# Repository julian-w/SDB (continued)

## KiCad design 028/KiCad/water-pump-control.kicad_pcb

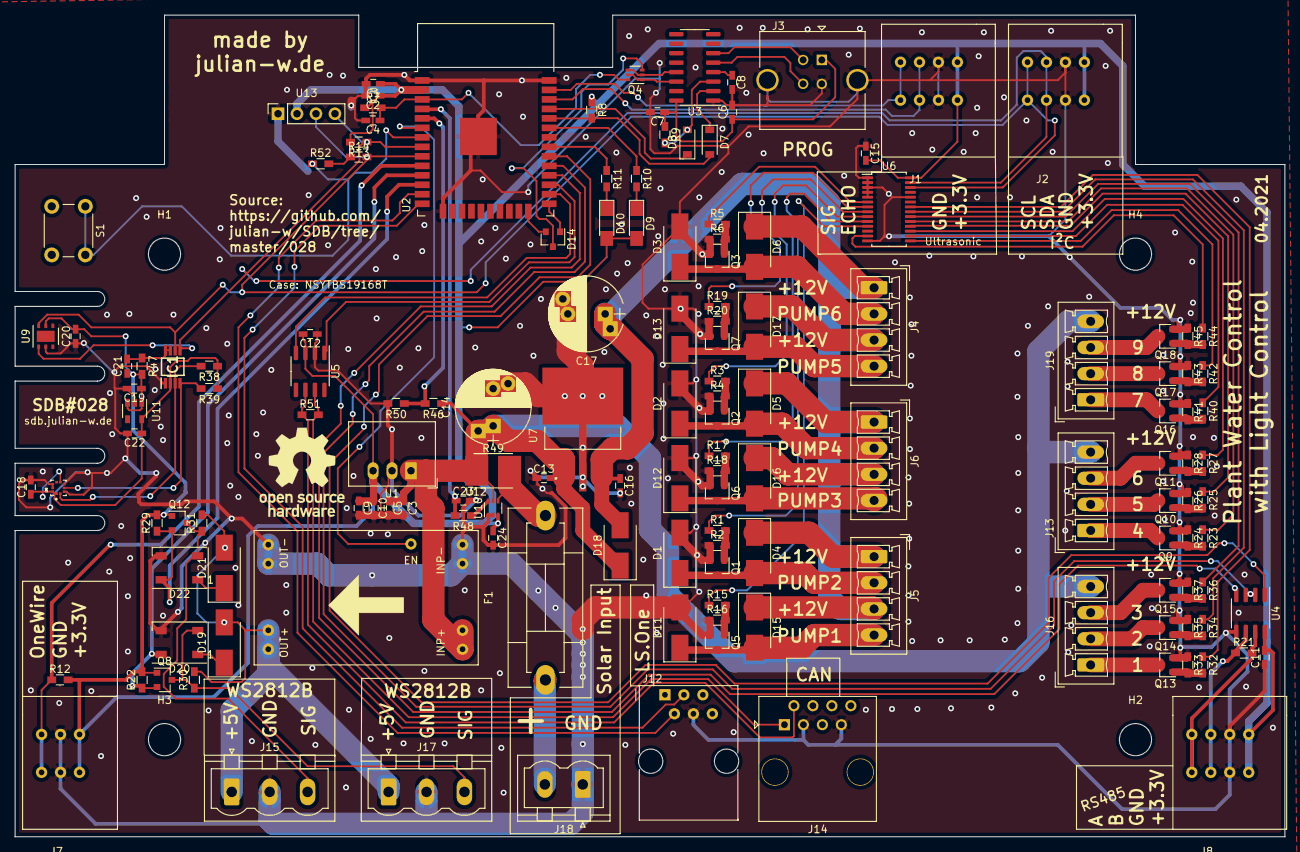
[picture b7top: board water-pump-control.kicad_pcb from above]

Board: 2 copper layers, 170.0 x 110.0 mm, 153 parts (0 on the bottom side), 101 nets.

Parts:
C1, C2, C5, C6, C7, C10, C11, C12, C13, C15, C16, C18, C20, C21: 100n; C_0603_HandSoldering
C3, C9: 10u; C_0603_HandSoldering
C4, C19, C22: 1u; C_0603_HandSoldering
C8: 10n; C_0603_HandSoldering
C14, C17: 100u; CP_Radial_D10.0mm_P5.00mm_P7.50mm
C23: 10nF; C_0603_HandSoldering
C24: 100nF; C_0603_HandSoldering
D1, D2, D3, D4, D5, D6, D11, D12, D13, D15, D16, D17, D18, D19, D21: 1N4004; D_SMB_Handsoldering
D7, D8: D; D_SOD-123
D9, D10: LED; LED_1206_HandSoldering
D14: BAT54C; SOT-23
D20, D22: WS2812B; LED_WS2812B_PLCC4_5.0x5.0mm_P3.2mm
F1: Fuse; Fuseholder5x20_horiz_SemiClosed_Casing10x25mm
H1, H2, H3, H4: MountingHole; MountingHole_4.3mm_M4
IC1: NVT2002DP,118; SOP65P490X110-8N
J1, J2, J8: Screw_Terminal_01x04; 4x2-2.54
J3: USB_B; USB_B_TE_5787834_Vertical
J4, J5, J6, J13, J16, J19: Screw_Terminal_01x04; PhoenixContact_MCV_1,5_4-G-3.5_1x04_P3.50mm_Vertical
J7: Screw_Terminal_01x03; 3x2-2.54
J12: 6P6C; RJ12_Amphenol_54601
J14: 8P8C; RJ45_OST_PJ012-8P8CX_Vertical
J15, J17: Screw_Terminal_01x03; PhoenixContact_MSTBVA_2,5_3-G-5,08_1x03_P5.08mm_Vertical
J18: BAT; PhoenixContact_MSTBVA_2,5_2-G-5,08_1x02_P5.08mm_Vertical
LOGO1: OSHW-LOGOL; OSHW-Logo_11.4x12mm_SilkScreen
Q1, Q2, Q3, Q5, Q6, Q7, Q9, Q10, Q11, Q13, Q14, Q15, Q16, Q17, Q18: IRLML6344; SOT-23
Q4: PUMX1; SOT-363_SC-70-6
Q8, Q12: BSS138; SOT-23
R1, R3, R5, R15, R17, R19, R23, R25, R27, R32, R34, R36, R40, R42, R44: 100; R_0603_HandSoldering
R2, R4, R6, R7, R8, R9, R16, R18, R20, R22, R24, R26, R28, R29, R30, R31, R33, R35, R37, R41, R43, R45, R52: 10k; R_0603_HandSoldering
R10, R11: 470; R_0603_HandSoldering
R12, R13, R14, R38, R39: 4.7k; R_0603_HandSoldering
R21, R51: 120; R_0603_HandSoldering
R46, R47: 200k; R_0603_HandSoldering
R48: 2.2k; R_0603_HandSoldering
R49: 2m; R_Bourns_CRE2512
R50: 20k; R_0603_HandSoldering
S1: SWITCH-MOMENTARY-2SMD; SW_PUSH_6mm_H13mm
U1: R-78HB3.3-0.5; Converter_DCDC_RECOM_R-78HB-0.5_THT
U2: ESP32-WROOM-32
U3: CH340C; SOIC-16_3.9x9.9mm_P1.27mm
U4: MAX14783ExS; SOIC-8_3.9x4.9mm_P1.27mm
U5: SN65HVD232; SOIC-8_3.9x4.9mm_P1.27mm
U6: PCA9685PW; TSSOP-28_4.4x9.7mm_P0.65mm
U7: LM2940S-12_NOPB; TO254P1524X483-4N
U8: BMP388; PQFN50P200X200X80-10N
U9: HDC1080; Texas_PWSON-N6
U10: INA186; SOT-363_SC-70-6
U11: MIC5504-1.8YM5; SOT-23-5
U12: 5V5A
U13: OLED_I2C; OLED_SSD1306_I2C_0.96

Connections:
5V_EN: U2.6, U12.5
+1V8: C18.1, C22.1, IC1.2, R38.1, R39.1, U8.1, U8.6, U8.10, U11.5
+3V3: C1.1, C2.1, C9.1, C10.1, C11.2, C12.2, C15.2, C19.1, C20.2, C21.1, C24.1, D9.2, D10.2, J1.4, J2.4, J7.3, J8.4, Q8.1, Q12.1, R7.1, R8.1, R12.2, R13.2, R14.1, R22.2, R29.2, R47.2, R52.2, U1.3, U2.2, U4.8, U5.3, U6.28, U9.5, U10.3, U11.1, U11.3, U13.2
+5V: D19.2, D21.2, J15.1, J17.1, R30.2, R31.2, U12.3
+5VP: C6.1, C7.1, J3.1, R9.1, U3.16
+12V: C16.1, C17.1, D4.1, D5.1, D6.1, D15.1, D16.1, D17.1, D18.2, J4.1, J4.3, J5.1, J5.3, J6.1, J6.3, U7.3
+15V: C3.1, C5.1, C13.2, C14.1, D18.1, J13.4, J16.4, J19.4, R46.1, R49.1, U1.1, U7.1, U10.5, U12.1
/SCL_1V8: IC1.3, R38.2, U8.2
/SDA_1V8: IC1.4, R39.2, U8.4
/SHUNT_LOAD_P: F1.2, R49.2, U10.4
CANH: J14.1, R51.2, U5.7
CANL: J14.2, R51.1, U5.6
CAN_D: U2.27, U5.1
CAN_R: U2.26, U5.4
GND: C1.2, C2.2, C3.2, C4.2, C5.2, C6.2, C7.2, C8.2, C9.2, C10.2, C11.1, C12.1, C13.1, C14.2, C15.1, C16.2, C17.2, C18.2, C19.2, C20.1, C22.2, C23.2, C24.2, D1.2, D2.2, D3.2, D11.2, D12.2, D13.2, D20.3, D22.3, IC1.1, J1.3, J2.3, J3.4, J3.5, J7.2, J8.3, J12.4, J14.3, J14.7, J15.2, J17.2, J18.1, Q1.2, Q2.2, Q3.2, Q5.2, Q6.2, Q7.2, Q9.2, Q10.2, Q11.2, Q13.2, Q14.2, Q15.2, Q16.2, Q17.2, Q18.2, R2.1, R4.1, R6.1, R16.1, R18.1, R20.1, R24.1, R26.1, R28.1, R33.1, R35.1, R37.1, R41.1, R43.1, R45.1, R50.2, U1.2, U2.1, U2.15, U2.38, U2.39, U3.1, U4.5, U5.2, U6.1, U6.2, U6.3, U6.4, U6.5, U6.14, U6.24, U7.2, U7.4, U8.3, U8.5, U8.8, U8.9, U9.2, U10.1, U10.2, U11.2, U12.2, U12.4, U13.1
IO0: D14.1, U2.25
IO2: D14.2, U2.24
I_LOAD: C23.1, R48.2, U2.4
LED1: R23.1, U6.19
LED2: R25.1, U6.18
LED3: R27.1, U6.17
LED4: R32.1, U6.22
LED5: R34.1, U6.21
LED6: R36.1, U6.20
LED7: R40.1, U6.16
LED8: R42.1, U6.15
LED9: R44.1, U6.13
LSONE_RX: J12.3, U2.14
LSONE_TX: J12.2, U2.13
unnamed: C8.1, U3.4
unnamed: C21.2, IC1.7, IC1.8, R47.1
unnamed: D1.1, D4.2, J5.2, Q1.3
unnamed: D2.1, D5.2, J6.2, Q2.3
unnamed: D3.1, D6.2, J4.2, Q3.3
unnamed: D7.1, U3.2
unnamed: D8.2, R9.2, U3.3
unnamed: D9.1, R10.2
unnamed: D10.1, R11.2
unnamed: D11.1, D15.2, J5.4, Q5.3
unnamed: D12.1, D16.2, J6.4, Q6.3
unnamed: D13.1, D17.2, J4.4, Q7.3
unnamed: D14.3, Q4.3
unnamed: D19.1, D20.1
unnamed: D21.1, D22.1
unnamed: F1.1, J18.2
unnamed: J3.2, U3.6
unnamed: J3.3, U3.5
unnamed: J13.1, Q9.3
unnamed: J13.2, Q10.3
unnamed: J13.3, Q11.3
unnamed: J16.1, Q13.3
unnamed: J16.2, Q14.3
unnamed: J16.3, Q15.3
unnamed: J19.1, Q16.3
unnamed: J19.2, Q17.3
unnamed: J19.3, Q18.3
unnamed: Q1.1, R1.2, R2.2
unnamed: Q2.1, R3.2, R4.2
unnamed: Q3.1, R5.2, R6.2
unnamed: Q4.1, Q4.5, U3.14
unnamed: Q4.2, Q4.4, U3.13
unnamed: Q5.1, R15.2, R16.2
unnamed: Q6.1, R17.2, R18.2
unnamed: Q7.1, R19.2, R20.2
unnamed: Q9.1, R23.2, R24.2
unnamed: Q10.1, R25.2, R26.2
unnamed: Q11.1, R27.2, R28.2
unnamed: Q13.1, R32.2, R33.2
unnamed: Q14.1, R34.2, R35.2
unnamed: Q15.1, R36.2, R37.2
unnamed: Q16.1, R40.2, R41.2
unnamed: Q17.1, R42.2, R43.2
unnamed: Q18.1, R44.2, R45.2
unnamed: R48.1, U10.6
unnamed: R52.1, S1.1, U2.7
ONEWIRE: J7.1, R12.1, U2.10
PUMP1: R1.1, U6.10
PUMP2: R3.1, U6.8
PUMP3: R5.1, U6.6
PUMP4: R15.1, U6.11
PUMP5: R17.1, U6.9
PUMP6: R19.1, U6.7
RESET: C4.1, Q4.6, R7.2, U2.3
RS485_A: J8.1, R21.2, U4.7
RS485_B: J8.2, R21.1, U4.6
RS485_DIR: U2.29, U4.2, U4.3
RS485_RX: U2.30, U4.1
RS485_TX: U2.28, U4.4
SCL: IC1.6, J2.1, R14.2, U2.9, U6.26, U9.6, U13.3
SDA: IC1.5, J2.2, R13.1, U2.8, U6.27, U9.1, U13.4
SONIC_ECHO: J1.2, U2.36
SONIC_TRIG: J1.1, U2.37
STAT1: R10.1, U2.33
STAT2: R11.1, U2.31
USB_RX: D8.1, U2.35
USB_TX: D7.2, R8.2, U2.34
V_LOAD: R46.2, R50.1, U2.5
WS2812_IN1: D22.4, Q12.2, R29.1, U2.12
WS2812_IN2: D20.4, Q8.2, R22.1, U2.11
WS2812_OUT1: D22.2, J15.3, Q12.3, R31.1
WS2812_OUT2: D20.2, J17.3, Q8.3, R30.1

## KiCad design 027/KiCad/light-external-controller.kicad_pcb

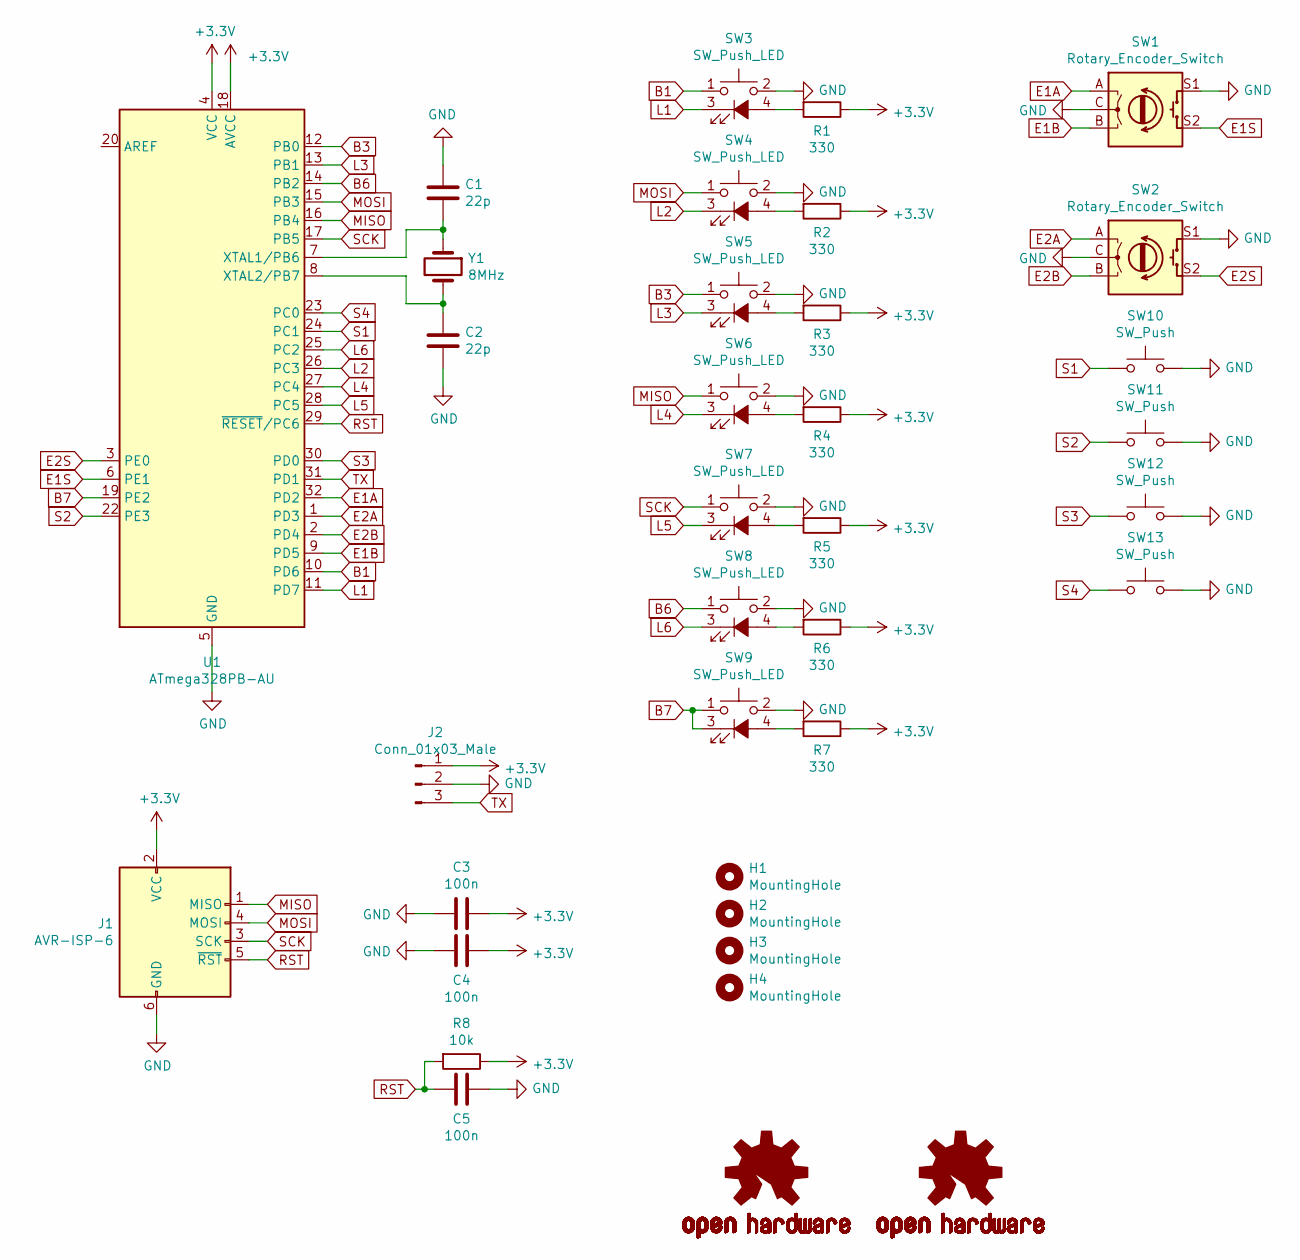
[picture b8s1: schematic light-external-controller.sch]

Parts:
C1, C2: 22p; C_0603_HandSoldering
C3, C4, C5: 100n; C_0603_HandSoldering
H1, H2, H3, H4: MountingHole; MountingHole_3.7mm
J1: AVR-ISP-6; IDC-Header_2x03_P2.54mm_Vertical
J2: Conn_01x03_Male; PinHeader_1x03_P2.54mm_Vertical
LOGO1, LOGO2: OSHW-LOGOL; OSHW-Logo_11.4x12mm_SilkScreen
R1, R2, R3, R4, R5, R6, R7: 330; R_0603
R8: 10k; R_0603
SW1, SW2: Rotary_Encoder_Switch; RotaryEncoder_Alps_EC11E-Switch_Vertical_H20mm
SW3, SW4, SW5, SW6, SW7, SW8, SW9: SW_Push_LED; ButtonWithLED
SW10, SW11, SW12, SW13: SW_Push; SW_PUSH-12mm
U1: ATmega328PB-AU; TQFP-32_7x7mm_P0.8mm
Y1: 8MHz; Crystal_HC49-4H_Vertical

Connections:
+3V3: C3.2, C4.2, J1.2 (VCC), J2.1, R1.1, R2.1, R3.1, R4.1, R5.1, R6.1, R7.1, R8.1, U1.4 (VCC), U1.18 (AVCC)
B1: SW3.1, U1.10 (PD6)
B3: SW5.1, U1.12 (PB0)
B6: SW8.1, U1.14 (PB2)
B7: SW9.1, SW9.3 (K), U1.19 (PE2)
E1A: SW1.A, U1.32 (PD2)
E1B: SW1.B, U1.9 (PD5)
E1S: SW1.S2, U1.6 (PE1)
E2A: SW2.A, U1.1 (PD3)
E2B: SW2.B, U1.2 (PD4)
E2S: SW2.S2, U1.3 (PE0)
GND: C1.1, C2.2, C3.1, C4.1, C5.2, J1.6 (GND), J2.2, SW1.C, SW1.S1, SW2.C, SW2.S1, SW3.2, SW4.2, SW5.2, SW6.2, SW7.2, SW8.2, SW9.2, SW10.2, SW11.2, SW12.2, SW13.2, U1.5 (GND), U1.21 (GND)
L1: SW3.3 (K), U1.11 (PD7)
L2: SW4.3 (K), U1.26 (PC3)
L3: SW5.3 (K), U1.13 (PB1)
L4: SW6.3 (K), U1.27 (PC4)
L5: SW7.3 (K), U1.28 (PC5)
L6: SW8.3 (K), U1.25 (PC2)
MISO: J1.1 (MISO), SW6.1, U1.16 (PB4)
MOSI: J1.4 (MOSI), SW4.1, U1.15 (PB3)
unnamed: C1.2, U1.7 (XTAL1/PB6), Y1.1
unnamed: C2.1, U1.8 (XTAL2/PB7), Y1.2
unnamed: R1.2, SW3.4 (A)
unnamed: R2.2, SW4.4 (A)
unnamed: R3.2, SW5.4 (A)
unnamed: R4.2, SW6.4 (A)
unnamed: R5.2, SW7.4 (A)
unnamed: R6.2, SW8.4 (A)
unnamed: R7.2, SW9.4 (A)
RST: C5.1, J1.5 (~RST), R8.2, U1.29 (~RESET~/PC6)
S1: SW10.1, U1.24 (PC1)
S2: SW11.1, U1.22 (PE3)
S3: SW12.1, U1.30 (PD0)
S4: SW13.1, U1.23 (PC0)
SCK: J1.3 (SCK), SW7.1, U1.17 (PB5)
TX: J2.3, U1.31 (PD1)

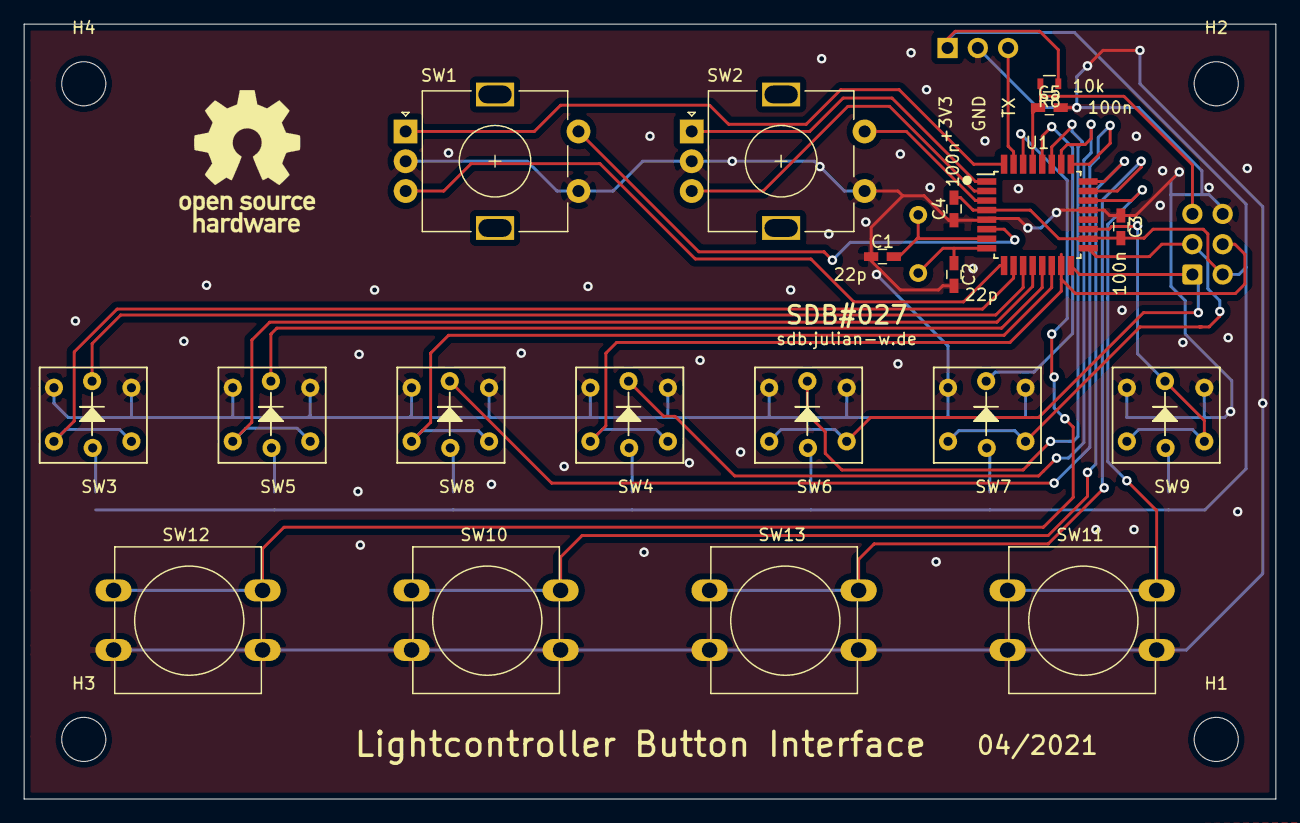
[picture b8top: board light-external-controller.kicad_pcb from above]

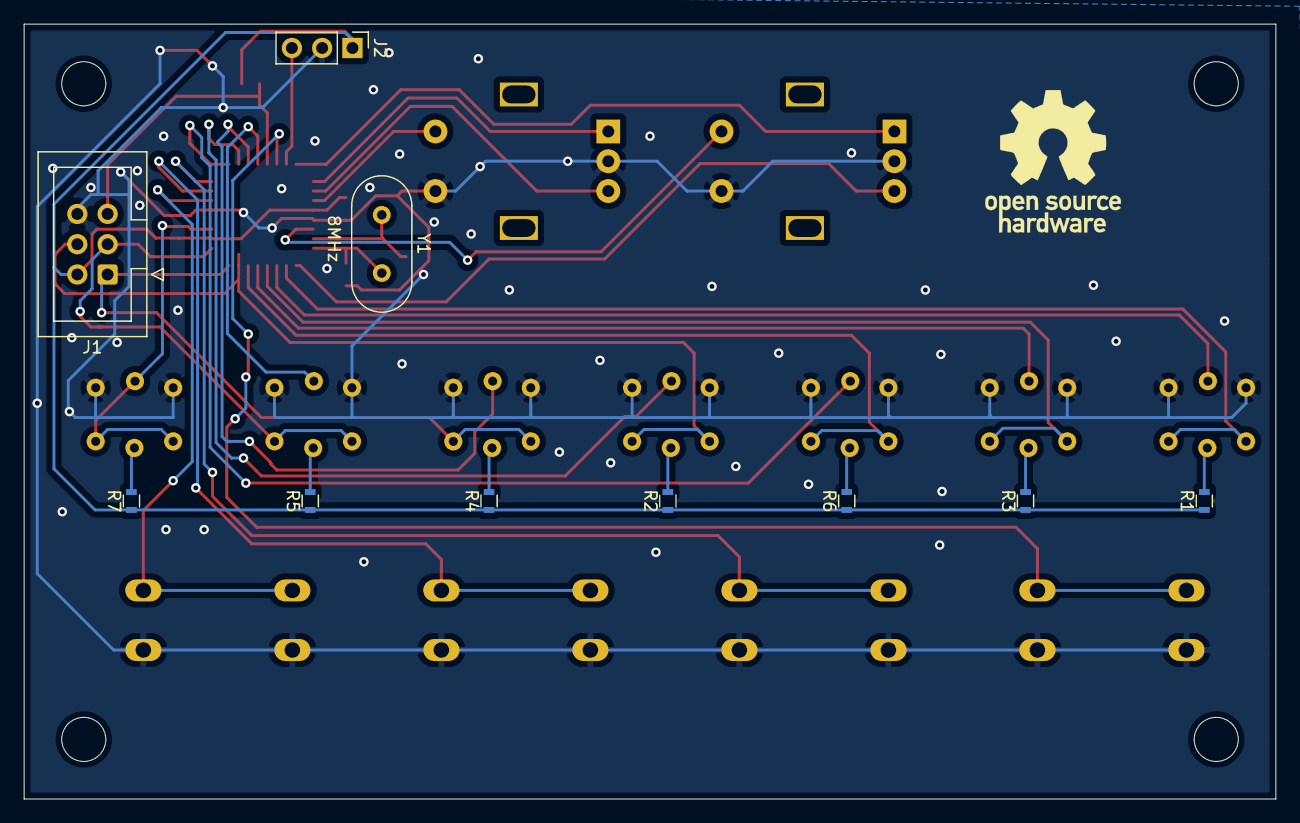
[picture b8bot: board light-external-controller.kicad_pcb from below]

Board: 2 copper layers, 105.0 x 65.0 mm, 36 parts (11 on the bottom side), 36 nets.

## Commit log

2021-04-18 inital push of data
2021-04-20 addin designs 025, 026 and 027
2021-04-25 adding SDB#028
2021-05-16 fixing wrong component in BOM
2021-06-22 adding SDB #29
2021-07-04 adding new boards to SDB (030, 031)
2021-07-23 updating partlist
2021-08-10 adding missing drill files
2022-11-01 updating SDB
2022-11-09 fixing naming SDA/SCL
